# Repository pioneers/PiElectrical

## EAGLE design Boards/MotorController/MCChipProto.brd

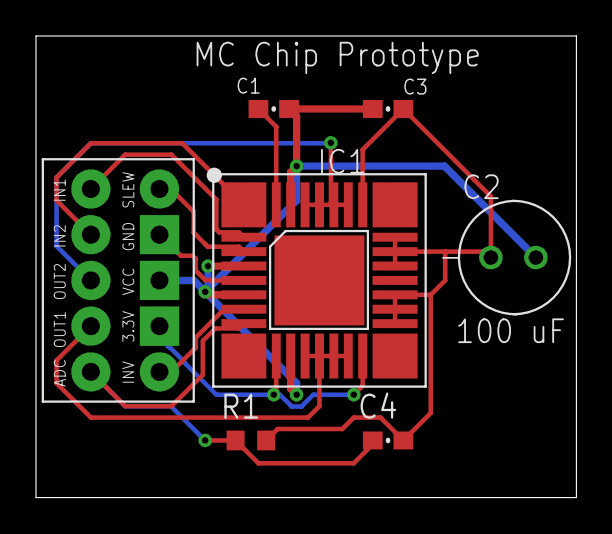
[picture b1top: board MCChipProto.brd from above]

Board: 2 copper layers, 30.0 x 25.6 mm, 8 parts (1 on the bottom side), 11 nets.

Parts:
C1: 33 nF; 0603-CAP
C2: 100 uF; .248"CAP_THRU
C3: 100 nF; 0603-CAP
C4: 1 uF; 0603-CAP
IC1: MC33926; PQFN-32
J1: MC BREAKOUT; 2X5PIN
R1: 200; R0603
U$1: PIE-LOGO-SMALL

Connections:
3.3V: IC1.10, IC1.16, J1.3.3V
ADC: C4.2, IC1.8, J1.ADC, R1.2
GND: C2.MINUS, C3.1, C4.1, IC1.5, IC1.18, IC1.19, IC1.20, IC1.22, IC1.23, IC1.24, IC1.26, J1.GND, R1.1
IN1: IC1.2, J1.IN1
IN2: IC1.1, J1.IN2
INV: IC1.7, J1.INV
unnamed: C1.1, IC1.32
OUT1: IC1.12, IC1.13, IC1.14, IC1.15, J1.OUT1
OUT2: IC1.27, IC1.28, IC1.29, IC1.30, J1.OUT2
SLEW: IC1.3, J1.SLEW
VCC: C1.2, C2.PLUS, C3.2, IC1.4, IC1.6, IC1.11, IC1.31, J1.VCC

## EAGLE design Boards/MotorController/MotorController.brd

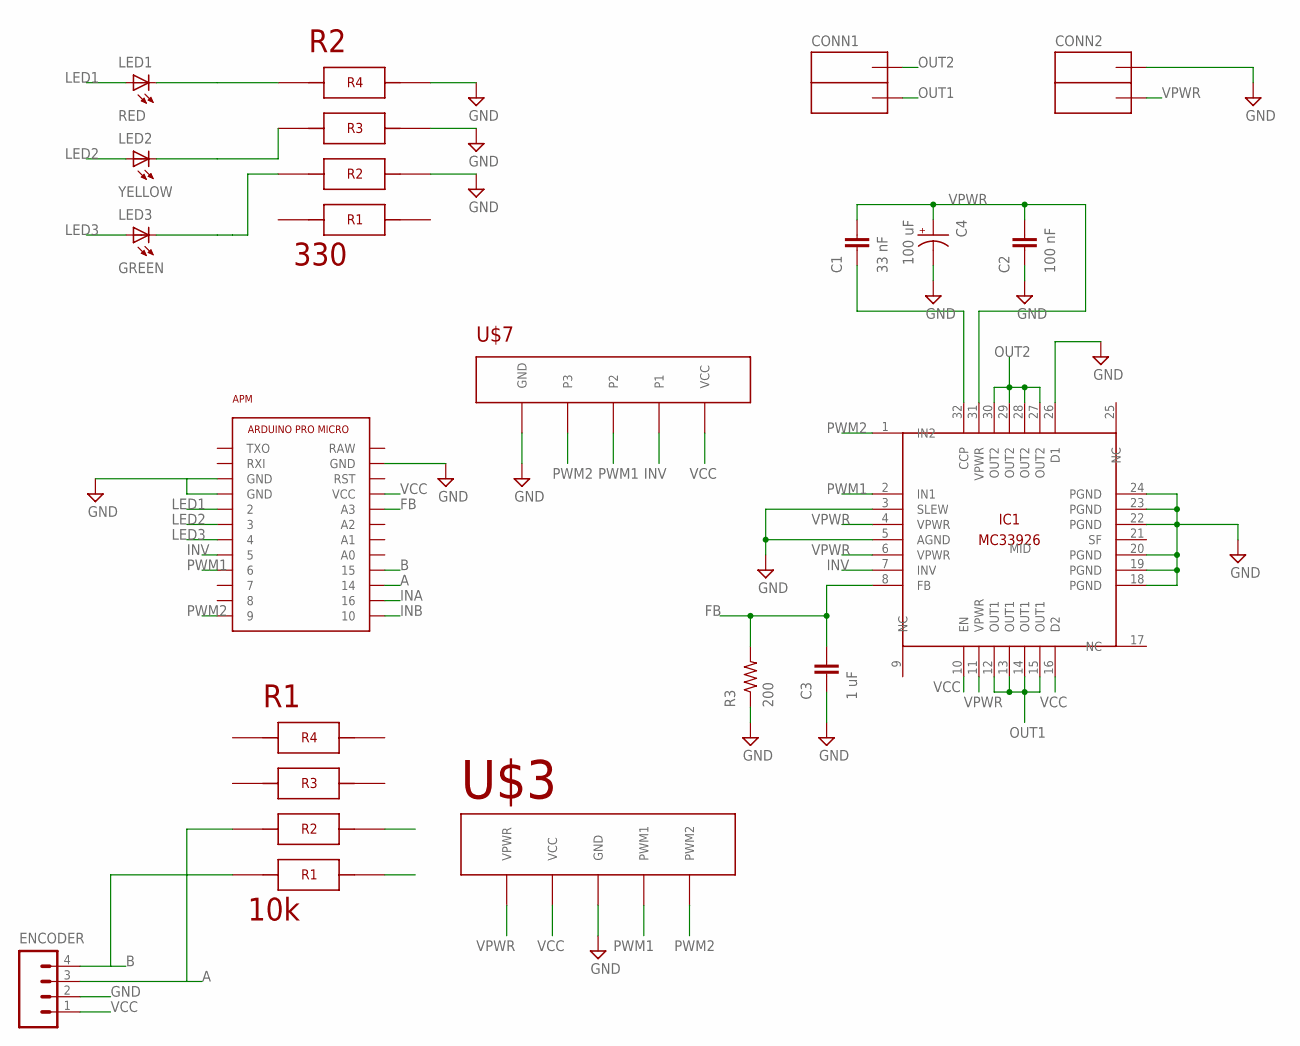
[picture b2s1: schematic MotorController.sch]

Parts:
APM: ARDUINO_PRO_MICRO
C1: 33 nF; 0603-CAP
C2: 100 nF; 0603-CAP
C3: 1 uF; 0603-CAP
C4: 100 uF; .248"CAP_THRU
CONN1, CONN2: ANDERSONVERTICAL; ANDERSON_VERTICAL
ENCODER: M041X04-MTA; 1X04-MTA
IC1: MC33926; PQFN-32
LED1: RED; LED-1206
LED2: YELLOW; LED-1206
LED3: GREEN; LED-1206
R1: 10k; 4X-0603
R2: 330; 4X-0603
R3: 200; R0603
U$3: 5XPOGO; 5XPOGO.40"
U$7: 5PIN5PIN_MC; 5PIN_MC

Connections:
A: APM.14, ENCODER.3, R1.7
B: APM.15, ENCODER.4, R1.8
CCP: C1.1, IC1.32 (CCP)
FB: APM.A3, C3.2, IC1.8 (FB), R3.2
GND: APM.GND@0 (GND), APM.GND@1 (GND), APM.GND@2 (GND), C2.1, C3.1, C4.MINUS (-), CONN2.PIN2 (OUTA), ENCODER.2, IC1.3 (SLEW), IC1.5 (AGND), IC1.18 (PGND), IC1.19 (PGND), IC1.20 (PGND), IC1.22 (PGND), IC1.23 (PGND), IC1.24 (PGND), IC1.26 (D1), R2.2, R2.3, R2.4, R3.1, U$3.GND, U$7.GND
INA: APM.16
INB: APM.10
INV: APM.5, IC1.7 (INV), U$7.INV (P1)
LED1: APM.2, LED1.A
LED2: APM.3, LED2.A
LED3: APM.4, LED3.A
unnamed: LED2.C, R2.6
unnamed: LED1.C, R2.5
unnamed: LED3.C, R2.7
OUT1: CONN1.PIN1 (OUTB), IC1.12 (OUT1), IC1.13 (OUT1), IC1.14 (OUT1), IC1.15 (OUT1)
OUT2: CONN1.PIN2 (OUTA), IC1.27 (OUT2), IC1.28 (OUT2), IC1.29 (OUT2), IC1.30 (OUT2)
PWM1: APM.6, IC1.2 (IN1), U$3.PWM1, U$7.PWM1 (P2)
PWM2: APM.9, IC1.1 (IN2), U$3.PWM2, U$7.PWM2 (P3)
VCC: APM.VCC, ENCODER.1, IC1.10 (EN), IC1.16 (D2), R1.1, R1.2, U$3.VCC, U$7.VCC
VPWR: C1.2, C2.2, C4.PLUS (+), CONN2.PIN1 (OUTB), IC1.4 (VPWR), IC1.6 (VPWR), IC1.11 (VPWR), IC1.31 (VPWR), U$3.VPWR

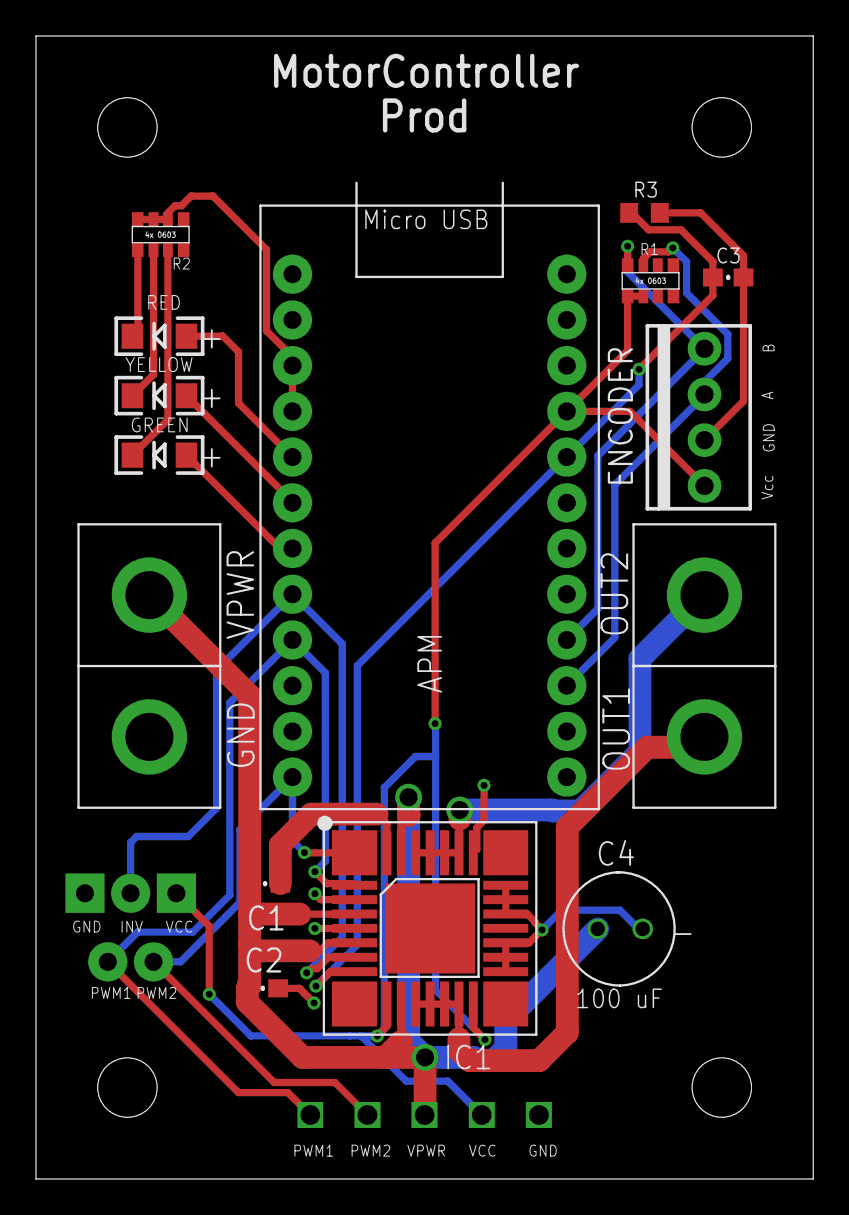
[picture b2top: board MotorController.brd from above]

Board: 2 copper layers, 43.2 x 63.5 mm, 22 parts (1 on the bottom side), 18 nets.

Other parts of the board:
U$1, U$2, U$5, U$6: STAND-OFF
U$4: OSHW-LOGO-S

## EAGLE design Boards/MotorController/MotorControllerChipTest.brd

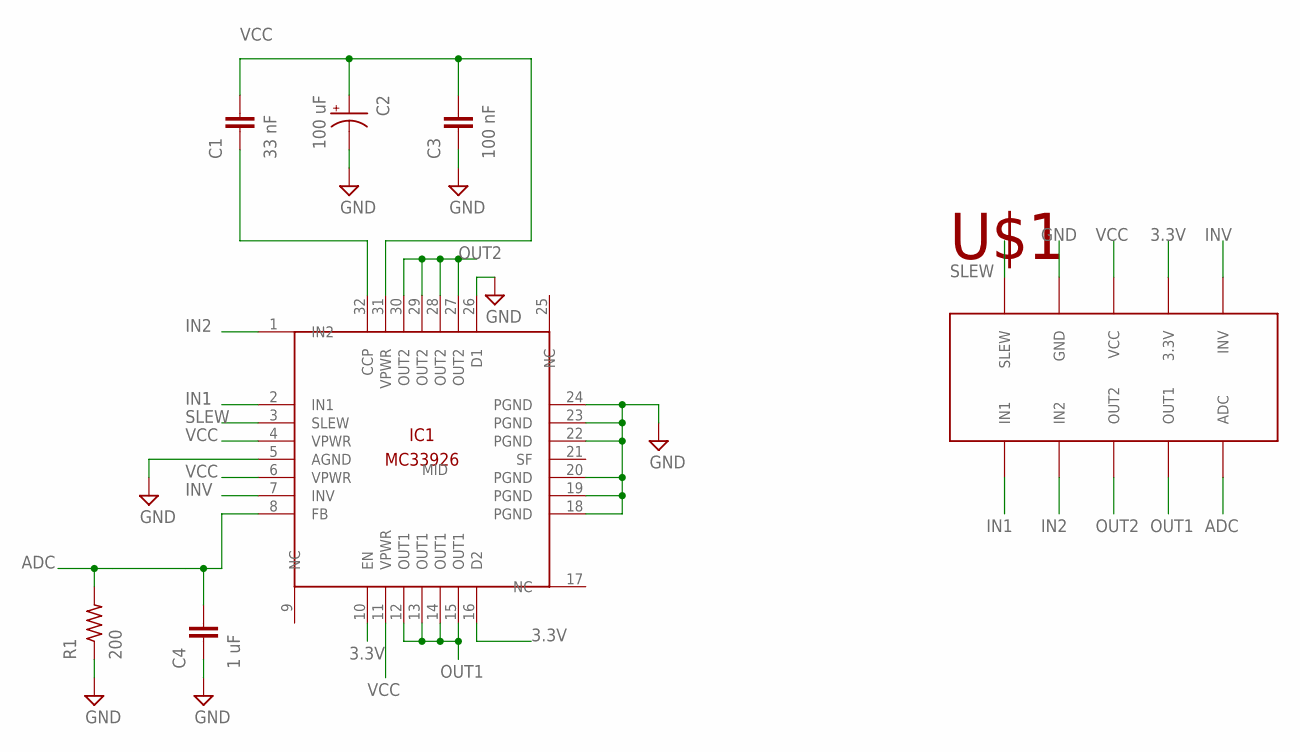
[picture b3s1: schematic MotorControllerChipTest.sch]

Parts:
C1: 33 nF; 0603-CAP
C2: 100 uF; .248"CAP_THRU
C3: 100 nF; 0603-CAP
C4: 1 uF; 0603-CAP
IC1: MC33926; PQFN-32
R1: 200; R0603
U$1: 2X5PIN

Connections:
3.3V: IC1.10 (EN), IC1.16 (D2), U$1.3.3V
ADC: C4.2, IC1.8 (FB), R1.2, U$1.ADC
GND: C2.MINUS (-), C3.1, C4.1, IC1.5 (AGND), IC1.18 (PGND), IC1.19 (PGND), IC1.20 (PGND), IC1.22 (PGND), IC1.23 (PGND), IC1.24 (PGND), IC1.26 (D1), R1.1, U$1.GND
IN1: IC1.2 (IN1), U$1.IN1
IN2: IC1.1 (IN2), U$1.IN2
INV: IC1.7 (INV), U$1.INV
unnamed: C1.1, IC1.32 (CCP)
OUT1: IC1.12 (OUT1), IC1.13 (OUT1), IC1.14 (OUT1), IC1.15 (OUT1), U$1.OUT1
OUT2: IC1.27 (OUT2), IC1.28 (OUT2), IC1.29 (OUT2), IC1.30 (OUT2), U$1.OUT2
SLEW: IC1.3 (SLEW), U$1.SLEW
VCC: C1.2, C2.PLUS (+), C3.2, IC1.4 (VPWR), IC1.6 (VPWR), IC1.11 (VPWR), IC1.31 (VPWR), U$1.VCC

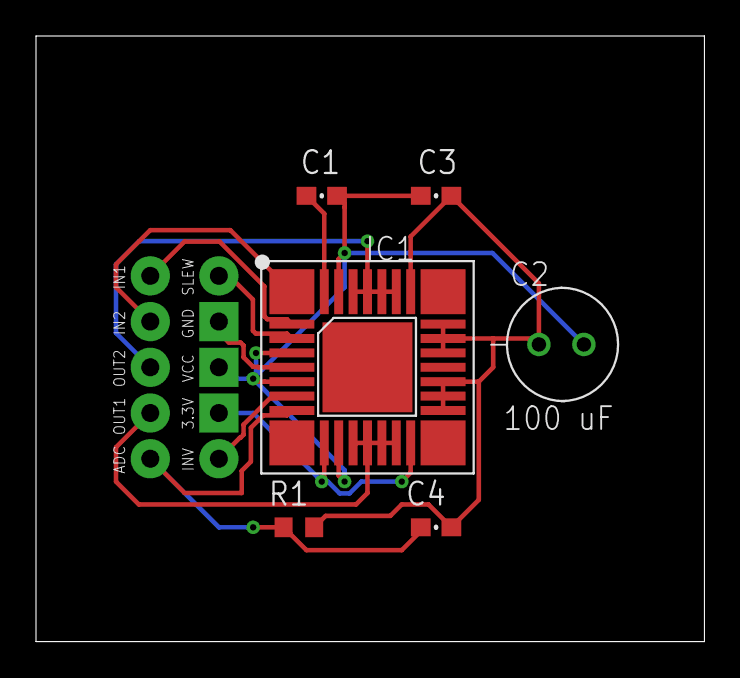
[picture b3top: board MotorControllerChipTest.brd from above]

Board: 2 copper layers, 37.1 x 33.6 mm, 7 parts (0 on the bottom side), 11 nets.

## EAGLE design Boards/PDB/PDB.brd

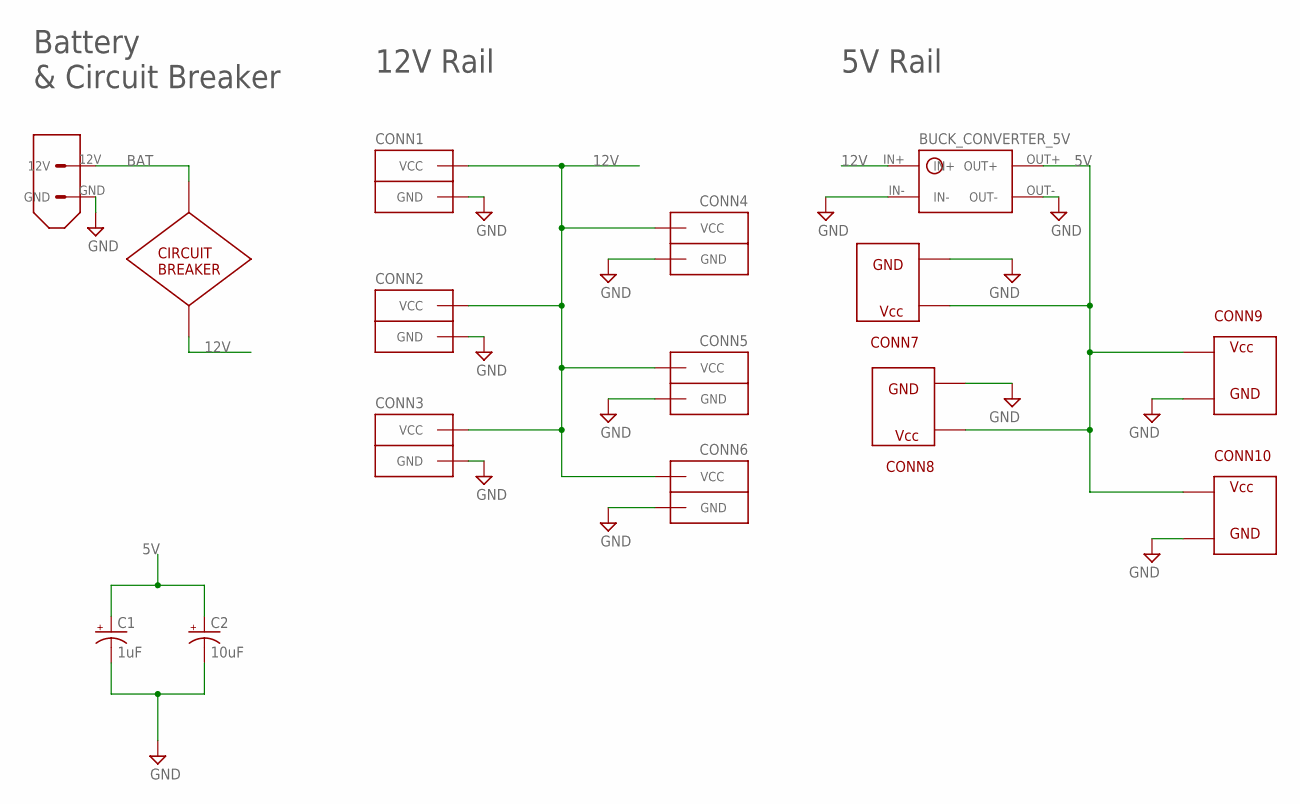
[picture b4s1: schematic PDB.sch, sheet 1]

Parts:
C1: 1uF; E5-5
C2: 10uF; E5-5
CIRCUIT_BREAKER: CIRC_BREAKER
CONN1, CONN2, CONN3, CONN4, CONN5, CONN6: ANDERSONVERTICAL; ANDERSON_VERTICAL
CONN7, CONN8, CONN9, CONN10: ATX
U$1: BUCK_CONVERTER_5V
XT60: XT60CONNECTOR

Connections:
5V: C1.+, C2.+, CONN7.P$1, CONN8.P$1, CONN9.P$1, CONN10.P$1, U$1.OUT+; also elsewhere on the board
12V: CIRCUIT_BREAKER.P$2, CONN1.PIN2 (VCC), CONN2.PIN2 (VCC), CONN3.PIN2 (VCC), CONN4.PIN2 (VCC), CONN5.PIN2 (VCC), CONN6.PIN2 (VCC), U$1.IN+
BAT: CIRCUIT_BREAKER.P$1, XT60.12V
GND: C1.-, C2.-, CONN1.PIN1 (GND), CONN2.PIN1 (GND), CONN3.PIN1 (GND), CONN4.PIN1 (GND), CONN5.PIN1 (GND), CONN6.PIN1 (GND), CONN7.P$2, CONN8.P$2, CONN9.P$2, CONN10.P$2, U$1.IN-, U$1.OUT-, XT60.GND; also elsewhere on the board

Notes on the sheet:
Battery & Circuit Breaker
12V Rail
5V Rail

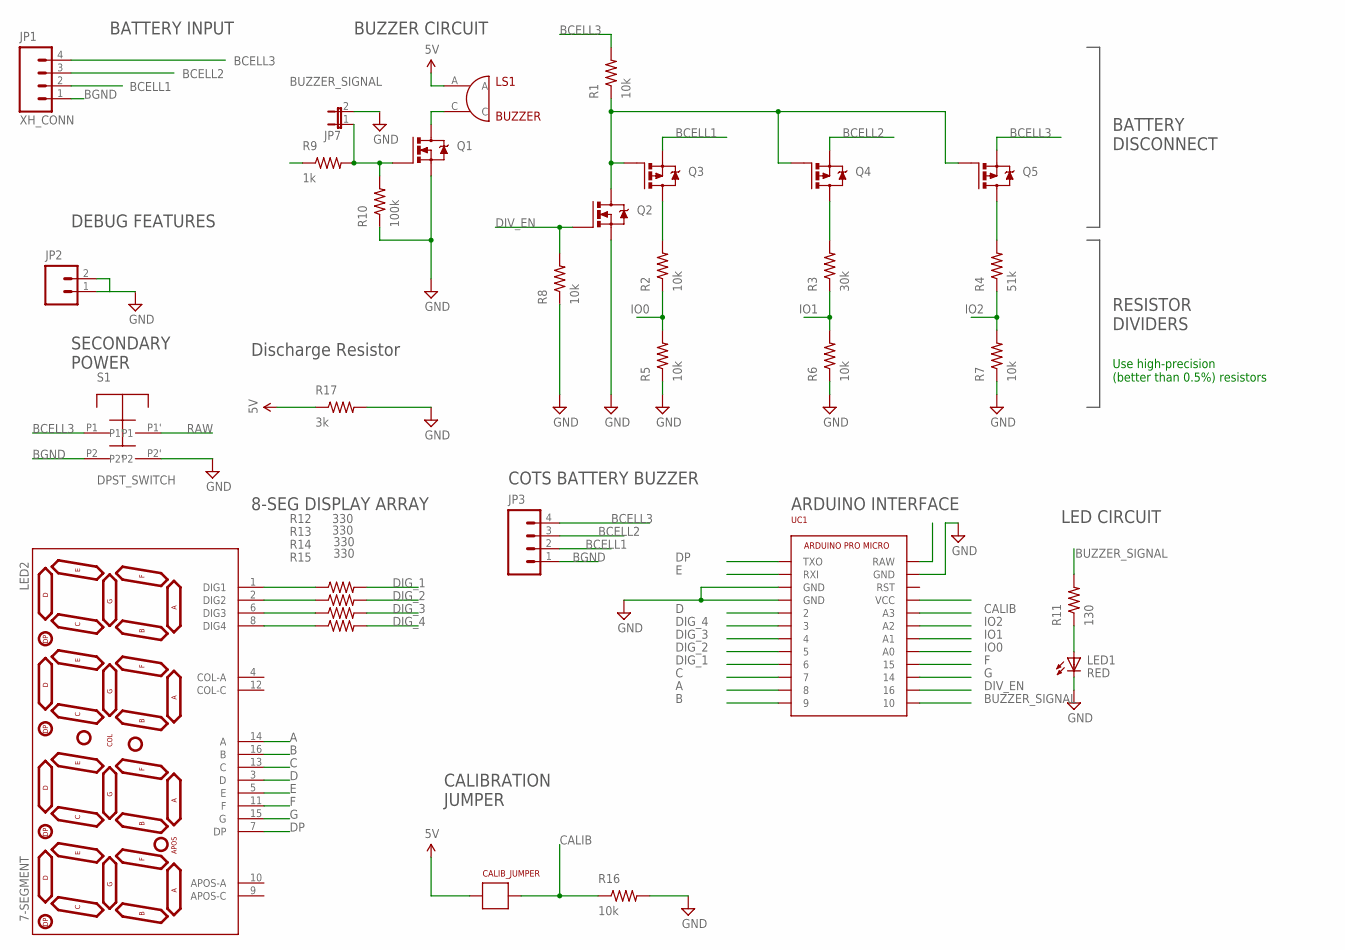
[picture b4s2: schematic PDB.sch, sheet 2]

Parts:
CALIB_JUMPER: JUMPER
JP1: XH_CONN; XH_CONNECTOR_4POS_2.5MM
JP2: M02PTH; 1X02
JP3: M04PTH; 1X04
JP7: JP1E; JP1
LED1: RED; LED-0805
LED2: 7-SEGMENT; 7-SEGMENT-4DIGIT-YOUNGSUN
LS1: BUZZER; BUZZER_MAGNETIC_5V_12MM_RADIAL
Q1: NMOS; SOT23-3
Q2: IRFML8244; SOT23-3
Q3, Q4, Q5: PMOS; SOT23-3
R1, R2, R5, R6, R7, R8, R16: 10k; R0603
R3: 30k; R0603
R4: 51k; R0603
R9: 1k; R0603
R10: 100k; R0603
R11: 130; R0603
R12, R13, R14, R15: 330; R0603
R17: 3k; R0603
S1: DPST_SWITCH; C&K_SWITCH
UC1: ARDUINO_PRO_MICRO

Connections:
5V: CALIB_JUMPER.P$1, LS1.A, R17.1, UC1.VCC; also elsewhere on the board
A: LED2.14 (A), UC1.8
B: LED2.16 (B), UC1.9
BCELL1: JP1.2, JP3.2, Q3.2 (S)
BCELL2: JP1.3, JP3.3, Q4.2 (S)
BCELL3: JP1.4, JP3.4, Q5.2 (S), R1.2, S1.P1
BGND: JP1.1, JP3.1, S1.P2
BUZZER_SIGNAL: R9.1, R11.2, UC1.10
C: LED2.13 (C), UC1.7
CALIB: CALIB_JUMPER.P$2, R16.1, UC1.A3
D: LED2.3 (D), UC1.2
DIG_1: R12.2, UC1.6
DIG_2: R13.2, UC1.5
DIG_3: R14.2, UC1.4
DIG_4: R15.2, UC1.3
DIV_EN: Q2.1 (G), R8.2, UC1.16
DP: LED2.7 (DP), UC1.TXO
E: LED2.5 (E), UC1.RXI
F: LED2.11 (F), UC1.15
G: LED2.15 (G), UC1.14
GND: JP2.1, JP2.2, JP7.2, LED1.C, Q1.2 (S), Q2.2 (S), R5.1, R6.1, R7.1, R8.1, R10.1, R16.2, R17.2, S1.P2', UC1.GND@0 (GND), UC1.GND@1 (GND), UC1.GND@2 (GND); also elsewhere on the board
IO0: R2.1, R5.2, UC1.A0
IO1: R3.1, R6.2, UC1.A1
IO2: R4.1, R7.2, UC1.A2
unnamed: Q2.3 (D), Q3.1 (G), Q4.1 (G), Q5.1 (G), R1.1
unnamed: Q3.3 (D), R2.2
unnamed: Q4.3 (D), R3.2
unnamed: Q5.3 (D), R4.2
unnamed: LS1.C, Q1.3 (D)
unnamed: JP7.1, Q1.1 (G), R9.2, R10.2
unnamed: LED1.A, R11.1
unnamed: LED2.1 (DIG1), R12.1
unnamed: LED2.2 (DIG2), R13.1
unnamed: LED2.6 (DIG3), R14.1
unnamed: LED2.8 (DIG4), R15.1
RAW: S1.P1', UC1.RAW

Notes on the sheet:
ARDUINO INTERFACE
LED CIRCUIT
BUZZER CIRCUIT
BATTERY INPUT
BATTERY DISCONNECT
RESISTOR DIVIDERS
Use high-precision (better than 0.5%) resistors
CALIBRATION JUMPER
SECONDARY POWER
8-SEG DISPLAY ARRAY
DEBUG FEATURES
Discharge Resistor
COTS BATTERY BUZZER

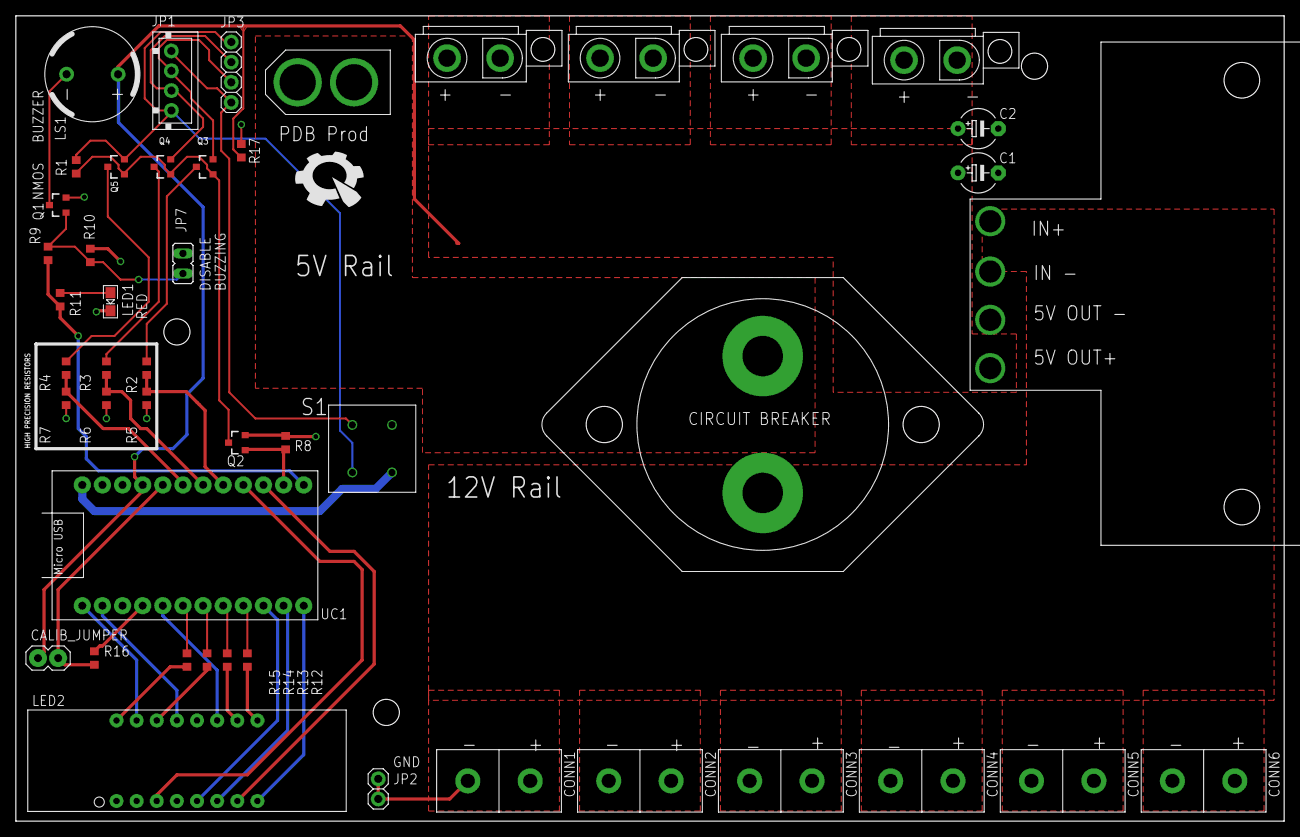
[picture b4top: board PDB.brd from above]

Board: 2 copper layers, 160.0 x 101.6 mm, 51 parts (0 on the bottom side), 38 nets.

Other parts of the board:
U$2, U$4, U$5: STAND-OFF
U$6: PIE-LOGO-SMALL

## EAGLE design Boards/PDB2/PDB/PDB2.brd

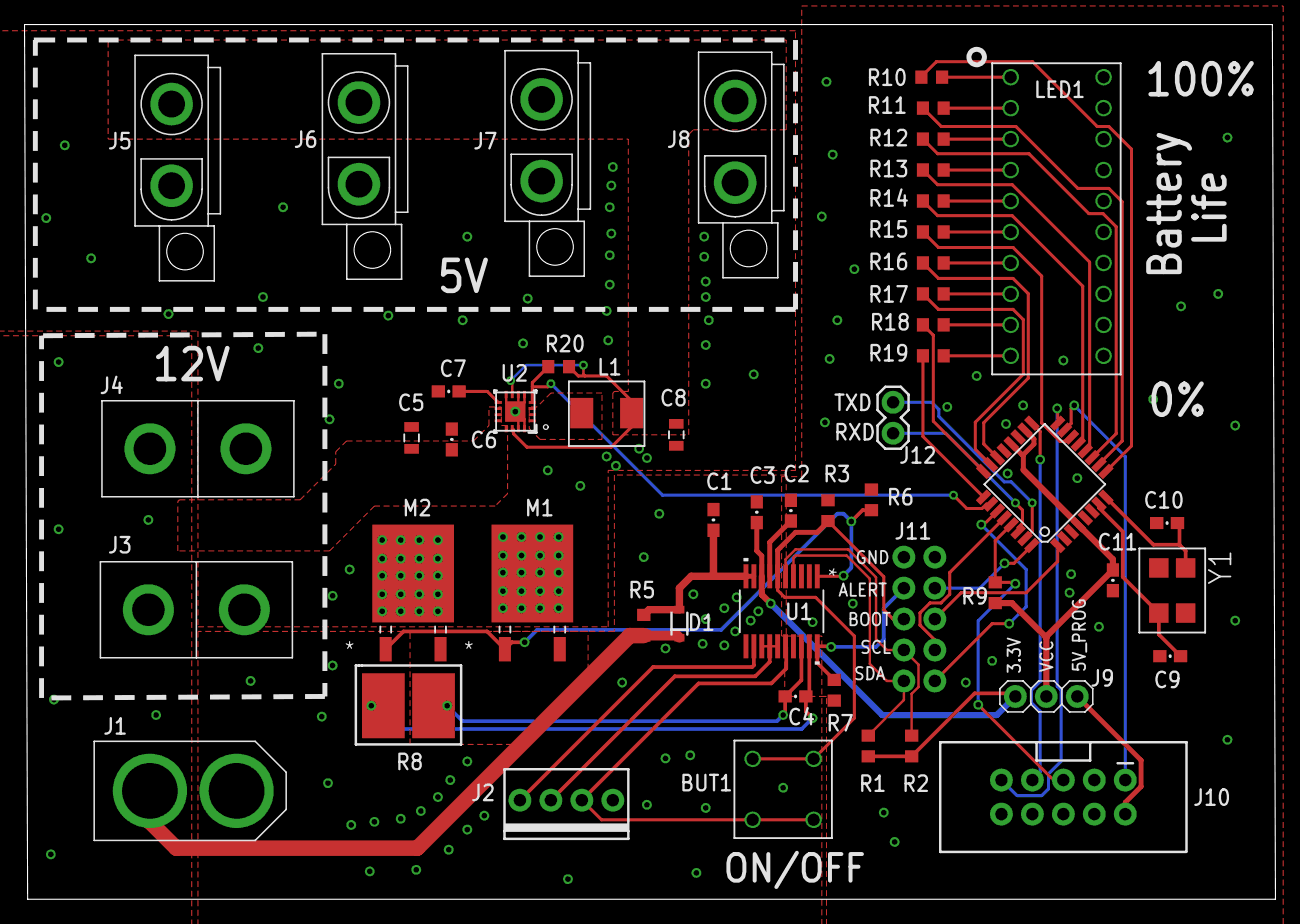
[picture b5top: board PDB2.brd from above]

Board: 2 copper layers, 102.6 x 71.8 mm, 52 parts (0 on the bottom side), 53 nets.

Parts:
BUT1: D6C90F1LFS; D6C_BUTTON
C1, C3: 2.2uF; 0603-CAP
C2, C11: 1uF; 0603-CAP
C4, C6: .1uF; 0603-CAP
C5: 10uF; 0805
C7: 1000pF; 0603-CAP
C8: 22uF; 0805
C9, C10: 18pF; 0603-CAP
D1: 220mV; SOD-323
J1: XT60CONNECTOR
J2: 1X04-MTA
J3, J4: ANDERSONVERTICAL; ANDERSON_VERTICAL
J5, J6, J7, J8: ATX
J9: 1X03
J10: AVR_SPI_PROG_5X2LOCK; 2X5-SHROUDED_LOCK
J11: 2X5_NOSILK
J12: 1X02
L1: 2.2uH; ASPI
LED1: BAR_SEGMENT_DISPLAY
M1, M2: STD20NF06LDPAK-M; DPAK-M
R1, R2: 3.3k; R0603
R3, R5, R9: 10k; R0603
R6: 5.6k; R0603
R7: 499k; R0603
R8: 5m; SMD_SHUNT
R10, R11, R12, R13, R14, R15, R16, R17, R18, R19: 220; R0603
R20: 100k; R0603
U1: BQ7692006PWRPW20-M; PW20-M
U2: Value; RGT0016C
U3: TQFP32-08
Y1: SMD_CRYSTAL

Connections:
3.3V: C3.2, J9.3, R1.2, R2.2, U1.8
5V: C8.2, J5.P$1, J6.P$1, J7.P$1, J8.P$1, L1.P$2, R20.2, U2.7, U2.14
5V_PROG: J9.1, J10.2
12V: C5.2, C6.2, D1.1, J1.12V, J3.PIN1, J4.PIN2, R5.2, U2.10, U2.11, U2.12, U2.13
ALERT: J11.8, R7.1, U1.20
BCELL1: BUT1.U1.1, BUT1.U1.2, J2.2, U1.16
BCELL2: J2.3, U1.13, U1.14, U1.15
BCELL3: J2.4, U1.12
BOOT: BUT1.U2.1, BUT1.U2.2, J11.6, R3.2, U1.6
BOOT_IN: J11.5, U3.1
CAP1: C2.2, U1.7
DSG: M1.1, M2.1, R6.2, U1.1
GND: C1.1, C2.1, C3.1, C4.2, C9.2, C10.2, C11.2, J1.GND, J2.1, J10.4, J10.6, J10.8, J10.10, J11.9, J11.10, LED1.BAR_DISPLAY10, LED1.BAR_DISPLAY11, LED1.BAR_DISPLAY12, LED1.BAR_DISPLAY13, LED1.BAR_DISPLAY14, LED1.BAR_DISPLAY15, LED1.BAR_DISPLAY16, LED1.BAR_DISPLAY17, LED1.BAR_DISPLAY18, LED1.BAR_DISPLAY19, R3.1, R6.1, R7.2, R8.P$1, U1.3, U1.17, U1.19, U3.5, U3.21, Y1.P1, Y1.P3
GND_OUT: C5.1, C6.1, C7.1, C8.1, J3.PIN2, J4.PIN1, J5.P$2, J6.P$2, J7.P$2, J8.P$2, M1.3, M2.3, U2.5, U2.6, U2.8, U2.15, U2.16, U2.17
LED1: R10.1, U3.9
LED2: R11.1, U3.10
LED3: R12.1, U3.11
LED4: R13.1, U3.12
LED5: R14.1, U3.13
LED6: R15.1, U3.14
LED7: R16.1, U3.22
LED8: R17.1, U3.23
LED9: R18.1, U3.24
LED10: R19.1, U3.25
MISO: J10.9, U3.16
MOSI: J10.1, U3.15
unnamed: J11.1, U3.27
unnamed: L1.P$1, U2.1, U2.2, U2.3
unnamed: C9.1, U3.7, Y1.P2
unnamed: C7.2, U2.9
unnamed: C10.1, U3.8, Y1.P0
unnamed: J11.3, U3.28
unnamed: J11.7, U3.32
unnamed: LED1.BAR_DISPLAY0, R10.2
unnamed: LED1.BAR_DISPLAY1, R11.2
unnamed: LED1.BAR_DISPLAY2, R12.2
unnamed: LED1.BAR_DISPLAY3, R13.2
unnamed: LED1.BAR_DISPLAY4, R14.2
unnamed: LED1.BAR_DISPLAY5, R15.2
unnamed: LED1.BAR_DISPLAY6, R16.2
unnamed: LED1.BAR_DISPLAY7, R17.2
unnamed: LED1.BAR_DISPLAY8, R18.2
unnamed: LED1.BAR_DISPLAY9, R19.2
PG: R20.1, U2.4, U3.26
RST: J10.5, R9.1, U3.29
RXD: J12.1, U3.30
SCK: J10.7, U3.17
SCL: J11.4, R2.1, U1.5
SDA: J11.2, R1.1, U1.4
SRP: C4.1, M1.2, M2.2, R8.P$2, U1.18
TXD: J12.2, U3.31
VCC: C11.1, J9.2, R9.2, U3.4, U3.18, U3.20
VIN: C1.2, D1.2, R5.1, U1.9, U1.10

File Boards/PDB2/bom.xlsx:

Qty | Value | Device | Package | Parts | Description | DESCRIPTION | DISTRIBUTOR | DISTRIBUTOR_PART_NUMBER | MANUFACTURER | MANUFACTURER_NAME | MANUFACTURER_PART_NO | MANUFACTURER_PART_NUMBER | NOTES | PACKAGE | PARTNUMBER | PIE-INT-REF-NUM | PROD_ID | REFDES | SF_ID | TYPE | VALUE | VENDOR
1 |  | ATMEGA328PB-AU | TQFP32-08 | U3
1 |  | CONN_02 | 1X02 | J12 | Multi connection point. Often used as Generic Header-pin footprint for 0.1 inch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
1 |  | CONN_05X2NO_SILK | 2X5_NOSILK | J11 | Multi connection point. Often used as Generic Header-pin footprint for 0.1 inch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
1 |  | ECX-53BSMDCRYSTAL | SMD_CRYSTAL | Y1 |  |  |  |  |  |  | ECS-80-18-30B-AGN-TR
1 |  | M03PTH | 1X03 | J9 | 3-pin 0.1-inch header and MTA connector |  |  |  |  |  |  |  |  |  |  | BULK-STOCK
1 |  | M041X04-MTA | 1X04-MTA | J2 | 4-pin 0.1-inch header and MTA connector |  |  |  |  |  |  |  |  |  |  | MTA
2 | .1uF | CAP0603-CAP | 0603-CAP | C4, C6 | Capacitor |  |  |  |  |  |  |  |  |  |  | CAPACITOR-GENERIC
1 | 1000pF | CAP0603-CAP | 0603-CAP | C7 | Capacitor |  |  |  |  |  |  |  |  |  |  | CAPACITOR-GENERIC
1 | 100k | R-US_R0603 | R0603 | R20 | RESISTOR, American symbol | RESISTOR, American symbol | DigiKey |  | Rohm Semiconductor |  |  |  | Cut Tape | R0603 |  |  |  |  |  |  | >VALUE
3 | 10k | R-US_R0603 | R0603 | R3, R5, R9 | RESISTOR, American symbol | RESISTOR, American symbol | DigiKey |  | Rohm Semiconductor |  |  |  | Cut Tape | R0603 |  |  |  |  |  |  | >VALUE
1 | 10uF | CAP0603-CAP | 0805-CAP | C5 | Capacitor |  |  |  |  |  |  |  |  |  |  | CAPACITOR-GENERIC
2 | 18pF | CAP0603-CAP | 0603-CAP | C9, C10 | Capacitor |  |  |  |  |  |  |  |  |  |  | CAPACITOR-GENERIC
2 | 1uF | CAP0603-CAP | 0603-CAP | C2, C11 | Capacitor |  |  |  |  |  |  |  |  |  |  | CAPACITOR-GENERIC
2 | 2.2uF | CAP0603-CAP | 0603-CAP | C1, C3 | Capacitor |  |  |  |  |  |  |  |  |  |  | CAPACITOR-GENERIC
1 | 2.2uH | ASPI-0530_INDUCTOR | ASPI | L1
10 | 220 | R-US_R0603 | R0603 | R10, R11, R12, R13, R14, R15, R16, R17, R18, R19 | RESISTOR, American symbol | RESISTOR, American symbol | DigiKey |  | Rohm Semiconductor |  |  |  | Cut Tape | R0603 |  |  |  |  |  |  | >VALUE
1 | 220mV | DIODESOD-323 | SOD-323 | D1 | Diode |  |  |  |  |  |  |  |  |  |  | DIODE
1 | 22uF | CAP0603-CAP | 0805-CAP | C8 | Capacitor |  |  |  |  |  |  |  |  |  |  | CAPACITOR-GENERIC
2 | 3.3k | R-US_R0603 | R0603 | R1, R2 | RESISTOR, American symbol | RESISTOR, American symbol | DigiKey |  | Rohm Semiconductor |  |  |  | Cut Tape | R0603 |  |  |  |  |  |  | >VALUE
1 | 499k | R-US_R0603 | R0603 | R7 | RESISTOR, American symbol | RESISTOR, American symbol | DigiKey |  | Rohm Semiconductor |  |  |  | Cut Tape | R0603 |  |  |  |  |  |  | >VALUE
1 | 5.6k | R-US_R0603 | R0603 | R6 | RESISTOR, American symbol | RESISTOR, American symbol | DigiKey |  | Rohm Semiconductor |  |  |  | Cut Tape | R0603 |  |  |  |  |  |  | >VALUE
1 | 5m | R-US_R2512 | R2512 | R8 | RESISTOR, American symbol |  |  |  |  |  | WSHM28185L000FEA‎ |  |  |  |  | RESISTOR-GENERIC
2 | ANDERSONVERTICAL | ANDERSONVERTICAL | ANDERSON_VERTICAL | J3, J4 | 2-pin 25A Anderson Connector |  |  |  |  |  |  |  |  |  |  | Anderson
4 | ATX | ATX | ATX | J5, J6, J7, J8 | ATX 2 Pin Connector
1 | AVR_SPI_PROG_5X2LOCK | AVR_SPI_PROG_5X2LOCK | 2X5-SHROUDED_LOCK | J10 | AVR 10-pin ICSP Header |  |  |  |  |  |  |  |  |  |  |  | CONN-08671 |  | PRT-08506
1 | BAR_SEGMENT_DISPLAY | BAR_SEGMENT_DISPLAY | BAR_SEGMENT_DISPLAY | LED1
1 | BQ7692006PWRPW20-M | BQ7692006PWRPW20-M | PW20-M | U1 |  |  |  |  |  |  |  | BQ7692006PWR |  |  |  |  |  |  |  |  |  | Texas Instruments
1 | D6C90F1LFS | D6C90F1LFS | D6C_BUTTON | BUT1
2 | STD20NF06LDPAK-M | STD20NF06LDPAK-M | DPAK-M | M1, M2 |  |  |  |  |  |  |  | STD20NF06L |  |  |  |  |  |  |  |  |  | STMicroelectronics
1 | Value | TPS62133RGTR | RGT0016C | U2 |  |  |  |  | Texas Instruments | Texas Instruments |  | TPS62133RGTR |  |  | TPS62133RGTR |  |  | RefDes |  | TYPE | Value
1 | XT60CONNECTOR | XT60CONNECTOR | XT60CONNECTOR | J1 | 12V XT60 power connector |  |  |  |  |  |  |  |  |  | PRT-10474

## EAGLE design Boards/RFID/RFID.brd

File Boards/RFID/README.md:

# RFID

Identifies [RFID chips](https://www.aliexpress.com/item/High-Quality-MFRC-522-RC522-RFID-Reader-RF-IC-Card-Inductive-Sensor-Module-For-Arduino-Module/32657638702.html?spm=2114.01010208.3.1.ePefNj&ws_ab_test=searchweb201556_0%2Csearchweb201602_5_10057_10056_10065_10068_10055_10067_10054_10069_10059_10058_418_10073_10017_10070_10060_10061_10052_10062_10053_10050_10051%2Csearchweb201603_7&btsid=cb39fcb9-9ace-4eec-a43a-83949f44e6b2)

[Documentation](https://github.com/miguelbalboa/rfid)

Pinouts:

RFID | Arduino Pro Micro
---- | -----------------
RST | 9
SDA | 10
MOSI | 16
MISO | 14
SCK | 15
3.3V | VCC
GND | GND

**Y9**: They worked fine, very stable and got a good yield rate. The enclosure could have been just a TAD bigger to accomodate for the USB connection.

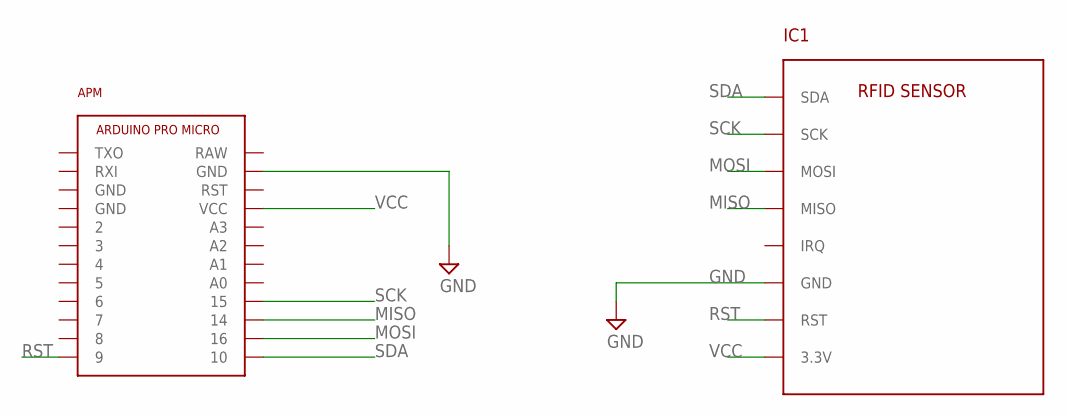
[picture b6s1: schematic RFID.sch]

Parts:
APM: ARDUINO_PRO_MICRO
IC1: RFID_SENSOR

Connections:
GND: APM.GND@2 (GND), IC1.GND
MISO: APM.14, IC1.MISO
MOSI: APM.16, IC1.MOSI
RST: APM.9, IC1.RST
SCK: APM.15, IC1.SCK
SDA: APM.10, IC1.SDA
VCC: APM.VCC, IC1.3.3V

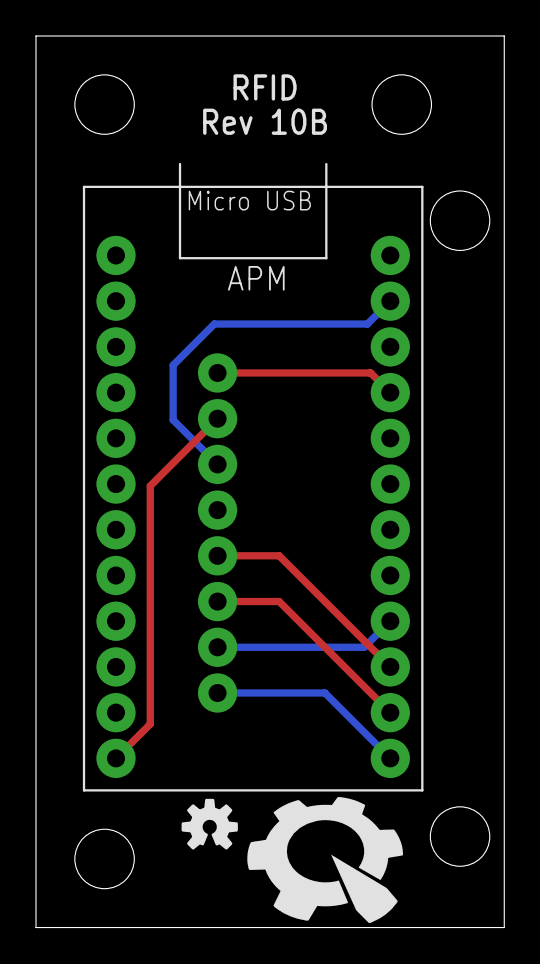
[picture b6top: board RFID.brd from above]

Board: 2 copper layers, 26.0 x 49.5 mm, 7 parts (1 on the bottom side), 7 nets.

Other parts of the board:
U$1: PIE-LOGO-SMALL
U$2, U$3, U$4: STAND-OFF
U$5: OSHW-LOGO-S

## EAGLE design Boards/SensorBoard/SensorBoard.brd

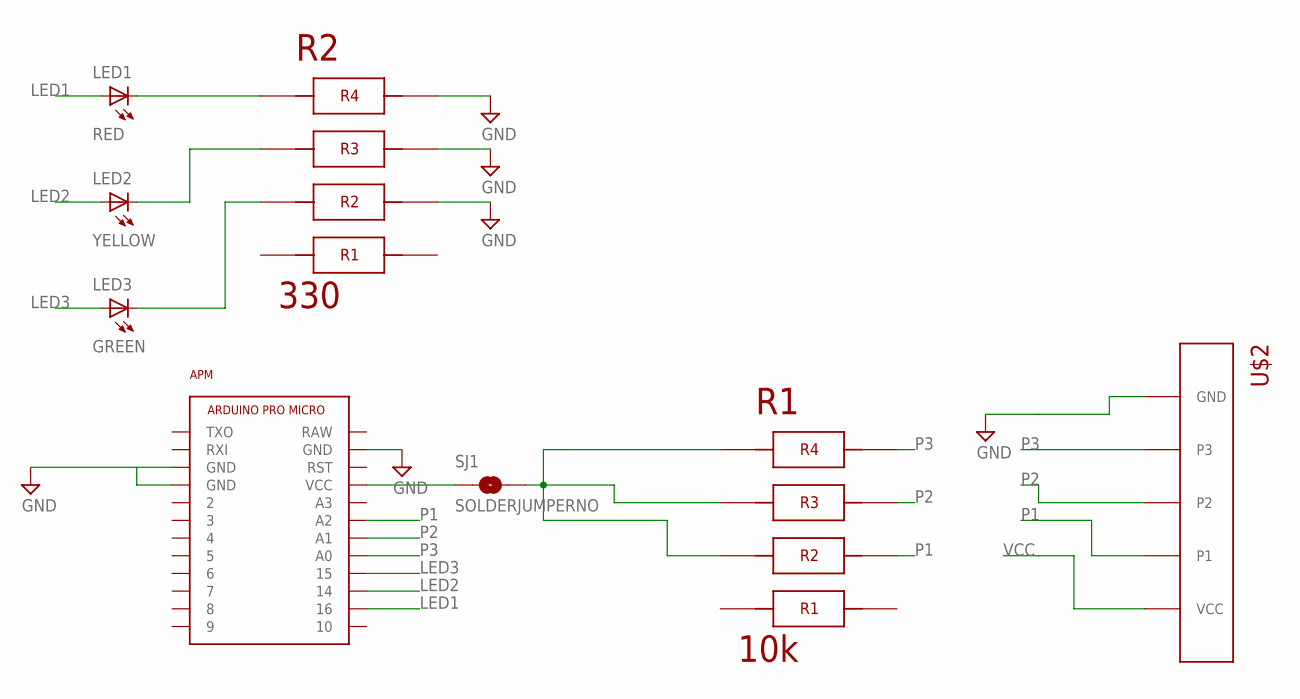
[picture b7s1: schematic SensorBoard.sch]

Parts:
APM: ARDUINO_PRO_MICRO
LED1: RED; LED-1206
LED2: YELLOW; LED-1206
LED3: GREEN; LED-1206
R1: 10k; 4X-0603
R2: 330; 4X-0603
SJ1: SOLDERJUMPERNO; SJ_2S-NO
U$2: 5PIN

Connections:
5V: R1.5, R1.6, R1.7, SJ1.2
GND: APM.GND@0 (GND), APM.GND@1 (GND), APM.GND@2 (GND), R2.2, R2.3, R2.4, U$2.GND
LED1: APM.16, LED1.A
LED2: APM.14, LED2.A
LED3: APM.15, LED3.A
unnamed: LED2.C, R2.6
unnamed: LED1.C, R2.5
unnamed: LED3.C, R2.7
P1: APM.A2, R1.2, U$2.P1
P2: APM.A1, R1.3, U$2.P2
P3: APM.A0, R1.4, U$2.P3
VCC: APM.VCC, SJ1.1, U$2.VCC

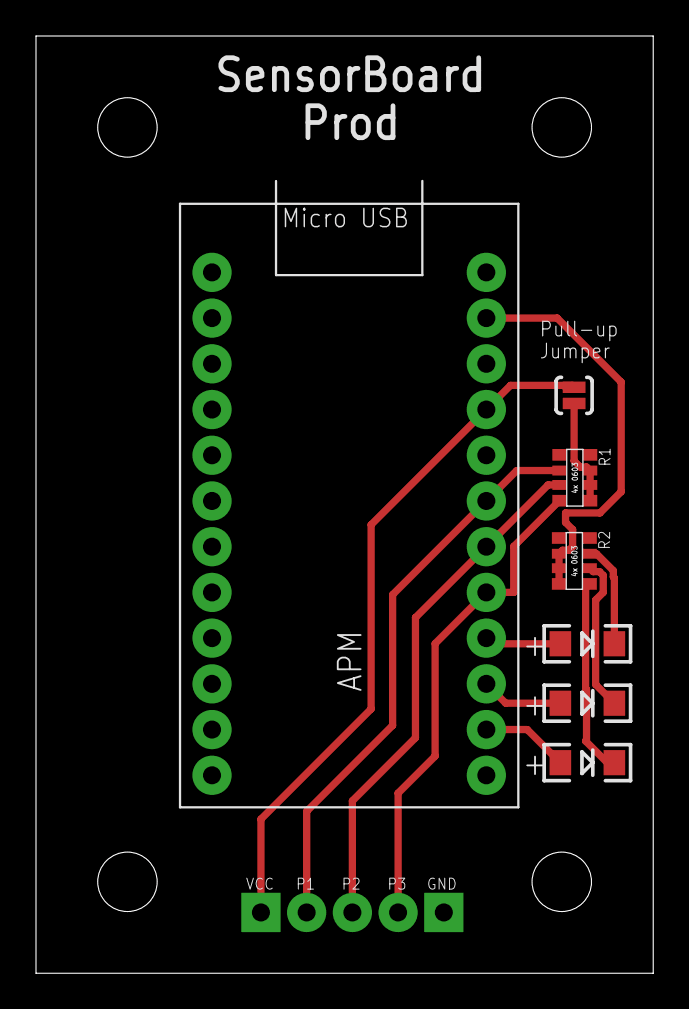
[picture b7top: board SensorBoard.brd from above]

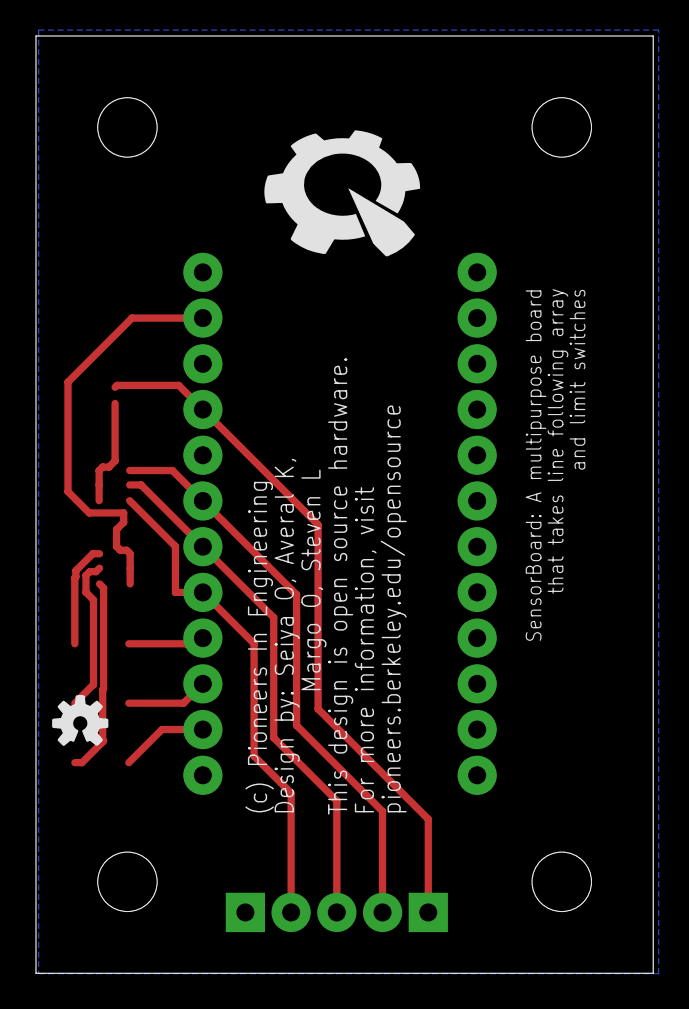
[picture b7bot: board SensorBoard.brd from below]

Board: 2 copper layers, 34.3 x 52.1 mm, 14 parts (2 on the bottom side), 12 nets.

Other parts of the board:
U$1, U$5, U$6, U$7: STAND-OFF
U$3: PIE-LOGO-SMALL
U$4: OSHW-LOGO-S

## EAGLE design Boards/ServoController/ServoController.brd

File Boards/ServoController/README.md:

#Servo Controller

Previous Named Koala Bear, controls the servo

Has 2 Servo Mounts, external 5 V and Max 1 Amp

Y9: We reduced the number of servos per board, no one complained, so we'll keep it this way to maintain a small formfactor. Think more about enclosure! It was the most stable board.

Y10: Avererorerol Kandala

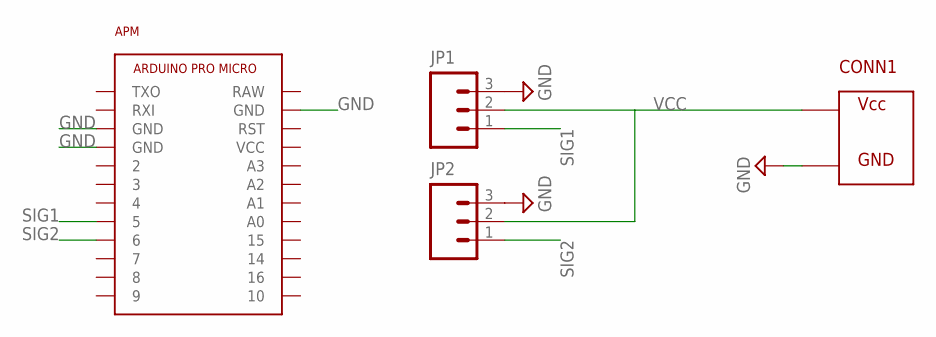
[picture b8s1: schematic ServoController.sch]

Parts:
APM: ARDUINO_PRO_MICRO
CONN1: ATX
JP1, JP2: M031X03-MTA; 1X03-MTA

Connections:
GND: APM.GND@0 (GND), APM.GND@1 (GND), APM.GND@2 (GND), CONN1.P$2, JP1.3, JP2.3
SIG1: APM.5, JP1.1
SIG2: APM.6, JP2.1
VCC: CONN1.P$1, JP1.2, JP2.2

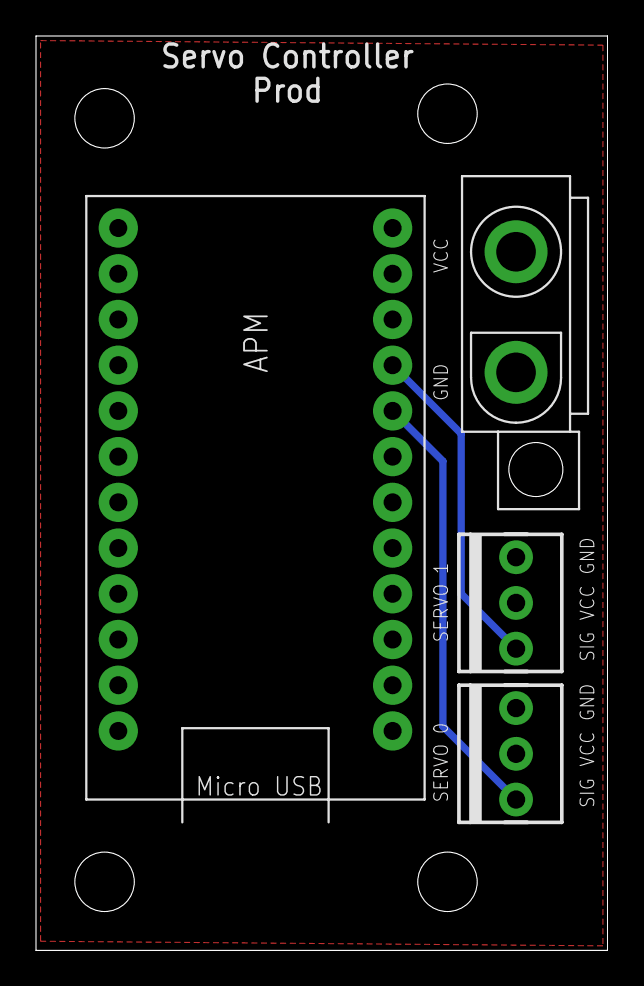
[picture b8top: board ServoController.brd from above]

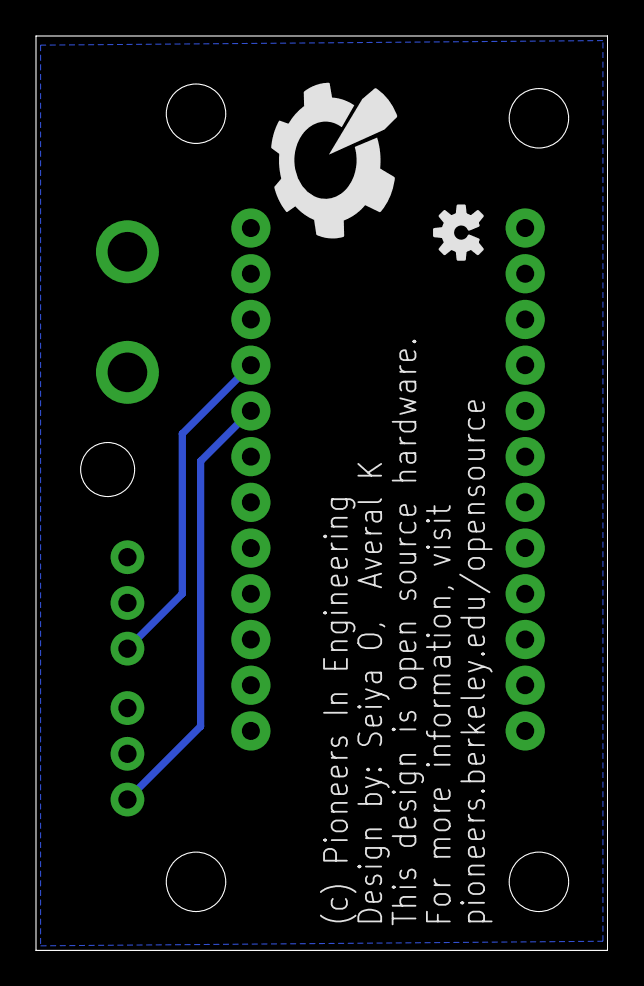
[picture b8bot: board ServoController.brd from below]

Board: 2 copper layers, 31.8 x 50.8 mm, 10 parts (2 on the bottom side), 4 nets.

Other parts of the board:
U$1, U$3, U$4, U$5: STAND-OFF
U$2: PIE-LOGO-SMALL
U$6: OSHW-LOGO-S

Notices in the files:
Boards/PDB/PDB.brd:
Copyright (c) 2016, Pioneers in Engineering
All rights reserved.
parts and their libraries:
SparkFun-Connectors: Licensing: Creative Commons ShareAlike 4.0 International - https://creativecommons.org/licenses/by-sa/4.0
